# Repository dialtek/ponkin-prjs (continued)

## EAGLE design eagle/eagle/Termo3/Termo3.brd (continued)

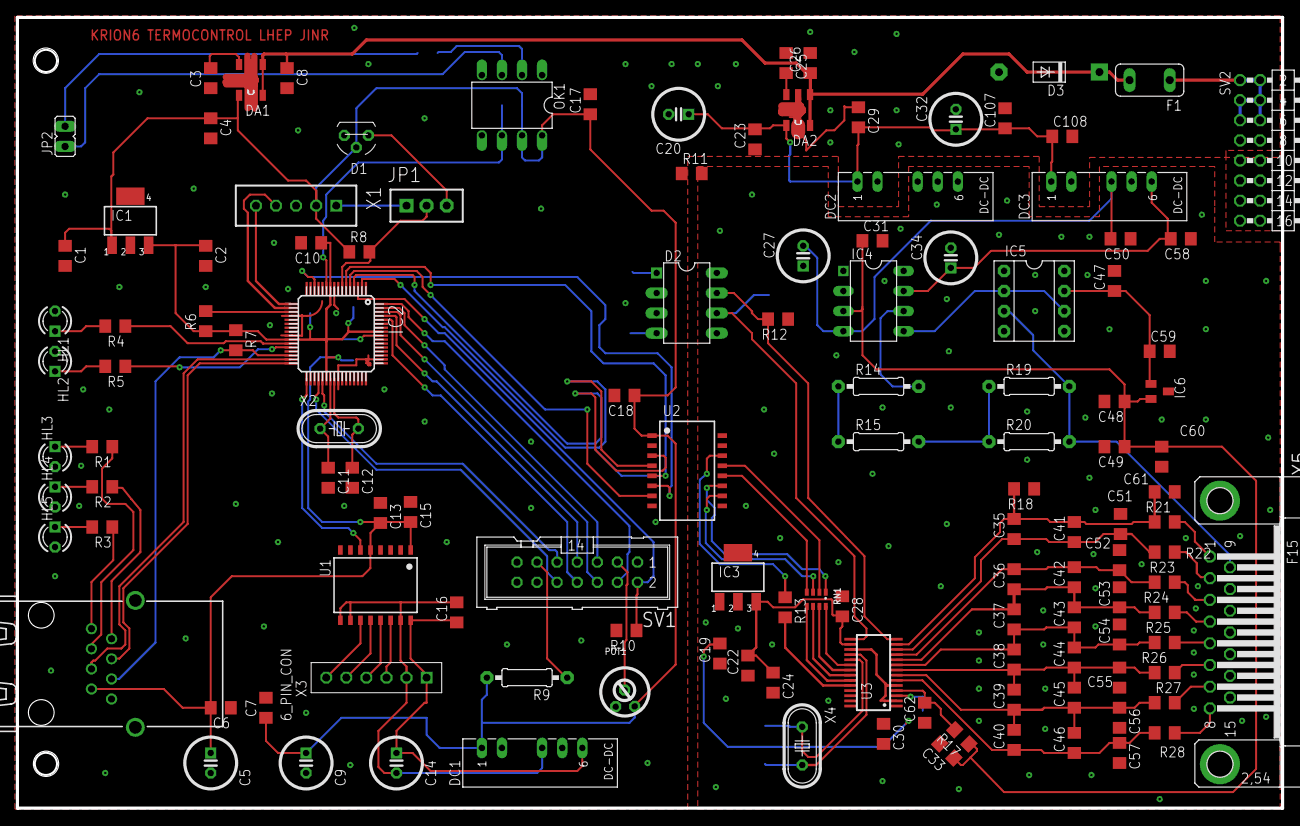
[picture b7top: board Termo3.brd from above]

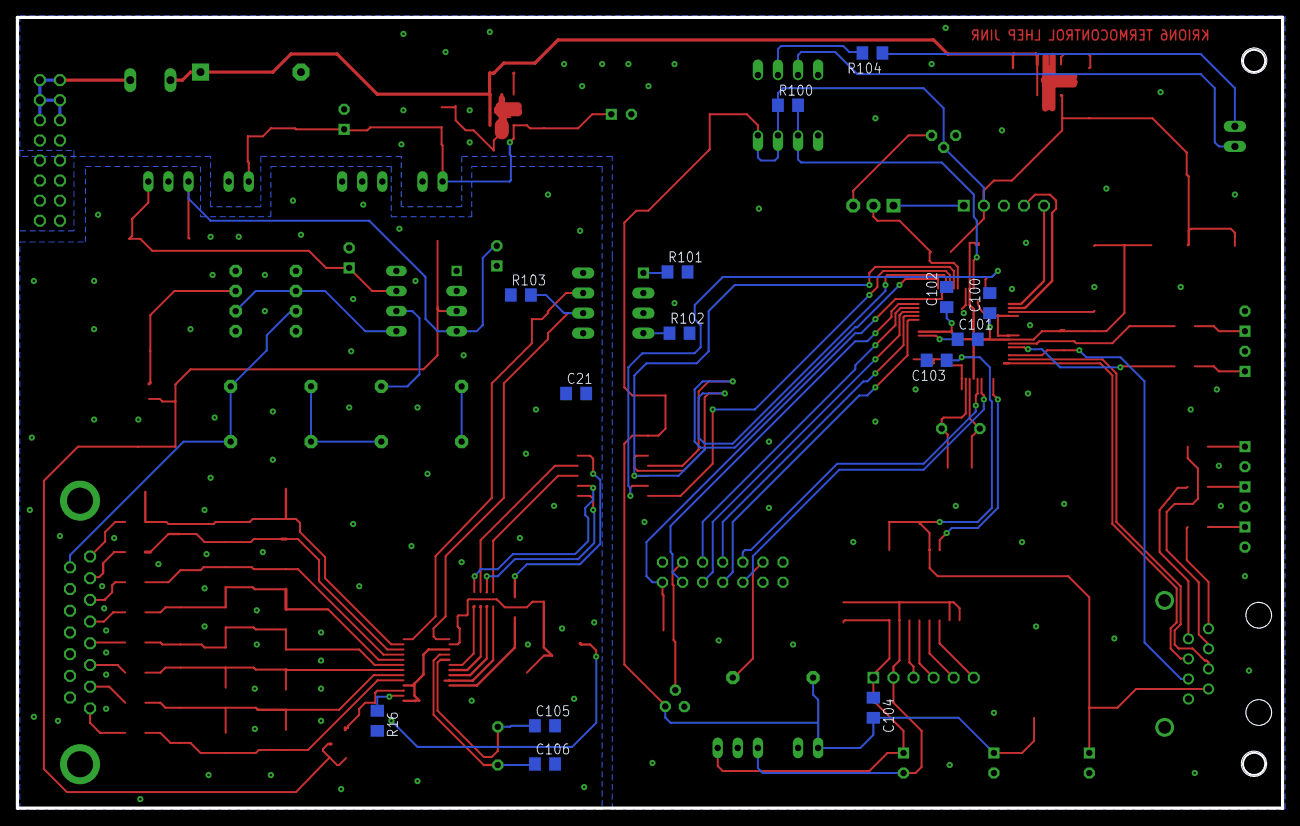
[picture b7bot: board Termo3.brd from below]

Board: 2 copper layers, 160.0 x 100.0 mm, 140 parts (14 on the bottom side), 103 nets.

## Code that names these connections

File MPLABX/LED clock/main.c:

#include <p18f25k80.h>
#include <delays.h>
//#include "myFUSES.h"

#pragma config RETEN = OFF      // VREG Sleep Enable bit (Ultra low-power regulator is Disabled (Controlled by REGSLP bit))
#pragma config INTOSCSEL = HIGH // LF-INTOSC Low-power Enable bit (LF-INTOSC in High-power mode during Sleep)
#pragma config SOSCSEL = HIGH   // SOSC Power Selection and mode Configuration bits (High Power SOSC circuit selected)
#pragma config XINST = OFF       // Extended Instruction Set (Enabled)

// CONFIG1H
#pragma config FOSC = HS1       // Oscillator (HS oscillator (Medium power, 4 MHz - 16 MHz))
#pragma config PLLCFG = OFF     // PLL x4 Enable bit (Disabled)
#pragma config FCMEN = OFF      // Fail-Safe Clock Monitor (Disabled)
#pragma config IESO = OFF       // Internal External Oscillator Switch Over Mode (Disabled)

// CONFIG2L
#pragma config PWRTEN = OFF     // Power Up Timer (Disabled)
#pragma config BOREN = SBORDIS  // Brown Out Detect (Enabled in hardware, SBOREN disabled)
#pragma config BORV = 3         // Brown-out Reset Voltage bits (1.8V)
#pragma config BORPWR = ZPBORMV // BORMV Power level (ZPBORMV instead of BORMV is selected)

// CONFIG2H
#pragma config WDTEN = SWDTDIS  // Watchdog Timer (WDT enabled in hardware; SWDTEN bit disabled)
#pragma config WDTPS = 1048576  // Watchdog Postscaler (1:1048576)

// CONFIG3H
#pragma config CANMX = PORTB    // ECAN Mux bit (ECAN TX and RX pins are located on RB2 and RB3, respectively)
#pragma config MSSPMSK = MSK7   // MSSP address masking (7 Bit address masking mode)
#pragma config MCLRE = ON       // Master Clear Enable (MCLR Enabled, RE3 Disabled)

// CONFIG4L
#pragma config STVREN = ON      // Stack Overflow Reset (Enabled)
#pragma config BBSIZ = BB2K     // Boot Block Size (2K word Boot Block size)

// CONFIG5L
#pragma config CP0 = OFF        // Code Protect 00800-01FFF (Disabled)
#pragma config CP1 = OFF        // Code Protect 02000-03FFF (Disabled)
#pragma config CP2 = OFF        // Code Protect 04000-05FFF (Disabled)
#pragma config CP3 = OFF        // Code Protect 06000-07FFF (Disabled)

// CONFIG5H
#pragma config CPB = OFF        // Code Protect Boot (Disabled)
#pragma config CPD = OFF        // Data EE Read Protect (Disabled)

// CONFIG6L
#pragma config WRT0 = OFF       // Table Write Protect 00800-03FFF (Disabled)
#pragma config WRT1 = OFF       // Table Write Protect 04000-07FFF (Disabled)
#pragma config WRT2 = OFF       // Table Write Protect 08000-0BFFF (Disabled)
#pragma config WRT3 = OFF       // Table Write Protect 0C000-0FFFF (Disabled)

// CONFIG6H
#pragma config WRTC = OFF       // Config. Write Protect (Disabled)
#pragma config WRTB = OFF       // Table Write Protect Boot (Disabled)
#pragma config WRTD = OFF       // Data EE Write Protect (Disabled)

// CONFIG7L
#pragma config EBTR0 = OFF      // Table Read Protect 00800-03FFF (Disabled)
#pragma config EBTR1 = OFF      // Table Read Protect 04000-07FFF (Disabled)
#pragma config EBTR2 = OFF      // Table Read Protect 08000-0BFFF (Disabled)
#pragma config EBTR3 = OFF      // Table Read Protect 0C000-0FFFF (Disabled)

// CONFIG7H
#pragma config EBTRB = OFF      // Table Read Protect Boot (Disabled)

#define CLK PORTCbits.RC3
#define DAT PORTCbits.RC5
#define CS1 PORTBbits.RB4


void delay(void)
{
  unsigned char i,j;
  for(i=0;i<200;i++)
  {
    j++;
  }
}

void init_command(unsigned int command_data)
{
  unsigned int i,j;
  command_data=command_data&0xfff;
  command_data=command_data<<4;
  CS1=1;
  Delay1TCY();
  CS1=0;
      for(i=0;i<12;i++)
  {
    CLK=0;
    j=command_data&0x8000;
    command_data=command_data<<1;
    j=j>>15;
    DAT=j;
    CLK=1;
  }
  CS1=1;
}

void set2416(void)
{
  //sys en
  init_command(0b100000000010);
  //led on
  init_command(0b100000000110);
  //blink on
//  init_command(0b100000010010);
  //master mode
  init_command(0b100000101110);
  //RC
  init_command(0b100000110110);
  //commons option
  //init_command(0b100001011110);//2416
  init_command(0b100001010110);//0832
  //pwm duty
  init_command(0b100101111110);
}

void MCU_Address_2416(unsigned char address)
{
  unsigned char i,temp;

  temp = 0x40;                                          //address has 7 bits. MSB fisrt

  for(i=0;i<7;i++)
  {
    CLK= 0;          //clk = 0 for data ready
              if((temp & address) == 0)
      DAT= 0;
    else
      DAT= 1;
    CLK= 1;        //clk = 1 for data write into 1632
    temp >>= 1;
  }
}


void MCU_Data_0832(unsigned char Data1,unsigned char Data2)
{
  unsigned char i,j,databuffer;
  for(j=0;j<4;j++)
  {
    databuffer=Data1;
          for(i=0 ; i<8 ; i++)
    {
      CLK=0;        //clk = 0 for data ready
          if(databuffer & 0x80)
            DAT=1;
      else
        DAT=0;
                  CLK=1;                          //clk = 1 for data write into 2
      databuffer=databuffer<<1;
    }
        databuffer=Data2;
          for(i=0 ; i<8 ; i++)
    {
      CLK=0;        //clk = 0 for data ready
          if(databuffer & 0x80)
            DAT=1;
      else
        DAT=0;
                  CLK=1;                          //clk = 1 for data write into 2
      databuffer=databuffer<<1;
    }

  }
}


void senddata1(void)
{
  unsigned char i,data1,data2;


        CS1=1;
      delay();
       CS1=0;
            delay();

      CLK=0;
      DAT=1;
      CLK=1;


      CLK=0;
      DAT=0;
      CLK=1;


      CLK=0;
      DAT=1;
      CLK=1;



 MCU_Address_2416(0x00);
            data1=0x55;
            data2=0x55;

        for(i=0;i<4;i++)
        MCU_Data_0832(data1,data2);


        delay();
            CS1=1;
}


void main(void) {
    //TRISA = 0x00;
    TRISCbits.TRISC3 = 0;
    TRISCbits.TRISC5 = 0;
    TRISBbits.TRISB4 = 0;
    set2416();
    delay();
    while(1){

             senddata1();
             Delay100TCYx(10);
    
    }
    

}

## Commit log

2018-01-19 new repo from cloud,2018 new PC
    2018 new PC
2018-02-12 modbus dev_id fix
2018-03-06 dialtek_modbus creation
2018-03-14 modbus input_reg fix
2018-03-28 turn_counter_fix
2018-03-28 turn_cnt_old_deleted
2018-05-04 mi1 id change fix
2018-07-05 timers modbus fix
2018-07-19 pic24_i2c eeprom fix
2018-09-25 turn counter fix
2018-11-29 end of november 2018
2018-12-03 PSD4 pump Modbus done
2019-01-31 2019
2019-02-28 02.2019
2019-03-07 RTOS modbus realied firt time!
2019-03-11 RTOS modbus fix+
2019-05-07 RTOS OW done!
2019-05-23 RTOS OW fix - cfg restore
2019-10-25 ИП704 контроллер
2019-11-21 nov 2019
2019-12-11 KORAD source main cmds done
2019-12-13 KORAD PS controller finish
2019-12-19 4 x LVDB read complete
2019-12-19 LVDB controller v1.0 finished
2019-12-20 LVDB controller UART freq set to 230kb
2020-02-05 PKT RS-485 negative signals meas. bug fix
2020-03-03 last update from old jinr PC
2020-03-05 jinr PC updated
2020-03-25 PBF module 1.4 modbus freeze fixed, ext trig led is ok
2020-07-31 HVCMM v1.0 completed
2020-08-11 final trash repo commit
